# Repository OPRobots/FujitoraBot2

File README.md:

# FujitoraBot2

Versión 2 de FujitoraBot renovando el hardware después de 5 años: un pelín más
rápido, con 24 sensores de línea, giroscopio MPU-6500 y diseño más modular.

## 🏆 Palmarés

| Competición | Resultado | Fecha |
|------------|-----------|-------|
| — | — | — |

## ⚙️ Hardware

| Componente | Detalle |
|-----------|---------|
| **Microcontrolador** | STM32F405RGT6 @ 168 MHz, Cortex-M4F |
| **Sensores** | 24× IR de línea (multiplexados 3×8:1), MPU-6500 (giro ±2000 dps, SPI) |
| **Motores** | 2× DC brushless con ESC BLHeli (OneShot125) |
| **Encoders** | 2× magnéticos en cuadratura (TIM3/TIM4) |
| **Batería** | LiPo 2S/3S, detección automática, divisor ×3.8673 |
| **Ventilador** | Control PWM independiente con rampa de aceleración |
| **Chasis** | PCB propia (KiCad) + impresión 3D |
| **Peso** | — |

## 💻 Software

| Componente | Detalle |
|-----------|---------|
| **Framework** | LibOpenCM3 |
| **Entorno** | PlatformIO |
| **Lenguaje** | C11 |
| **Frecuencia control** | 1000 Hz (TIM5) |
| **Algoritmo** | PID en cascada (velocidad + ángulo + sensores de línea) |
| **Odometría** | Encoders + giroscopio, integración de posición X/Y/θ |
| **Debug** | USART3 @ 115200 + MacroArray (30k registros de telemetría) |

## 📚 Documentación

La documentación técnica completa está en [docs/](docs/):

- [Hardware](docs/01-hardware.md) — MCU, pinout, sensores, actuadores, chasis
- [Arquitectura Software](docs/02-software-architecture.md) — ISRs, DMA, prioridades, flujo
- [Sensores](docs/03-sensors.md) — 24 IR multiplexados, MPU-6500, filtros
- [Movimiento](docs/04-movement.md) — Motores BLHeli, OneShot125, ventilador
- [Control PID](docs/05-control-system.md) — PID cascada, ant-windup, arranque
- [Menú](docs/06-menu-system.md) — Navegación, perfiles, calibración/debug
- [Debug](docs/07-debug-system.md) — USART, macroarray, modos de diagnóstico
- [Calibración](docs/08-calibration.md) — Giroscopio Z, sensores IR, EEPROM
- [EEPROM](docs/09-storage.md) — Flash sector 11, layout de datos
- [Encoders y Giroscopio](docs/10-encoders-gyro.md) — Odometría, MPU-6500, fusión
- [Batería y LEDs](docs/11-battery-leds.md) — Medición, 2S/3S, indicadores
- [Cinemática](docs/12-kinematics.md) — 6 perfiles de velocidad predefinidos
- [Problemas Conocidos](docs/13-known-issues.md) — Issues y bugs documentados

## 🎥 Vídeos

<!-- Enlaces a vídeos del robot en acción -->

## 🔧 Stack Tecnológico

| Herramienta | Tecnología |
|------------|-----------|
| **Microcontrolador** | STM32F405RGT6 |
| **Framework** | LibOpenCM3 |
| **IDE / Build** | PlatformIO |
| **Lenguaje** | C11 |
| **PCB** | KiCad |
| **3D** | SketchUp + STL |

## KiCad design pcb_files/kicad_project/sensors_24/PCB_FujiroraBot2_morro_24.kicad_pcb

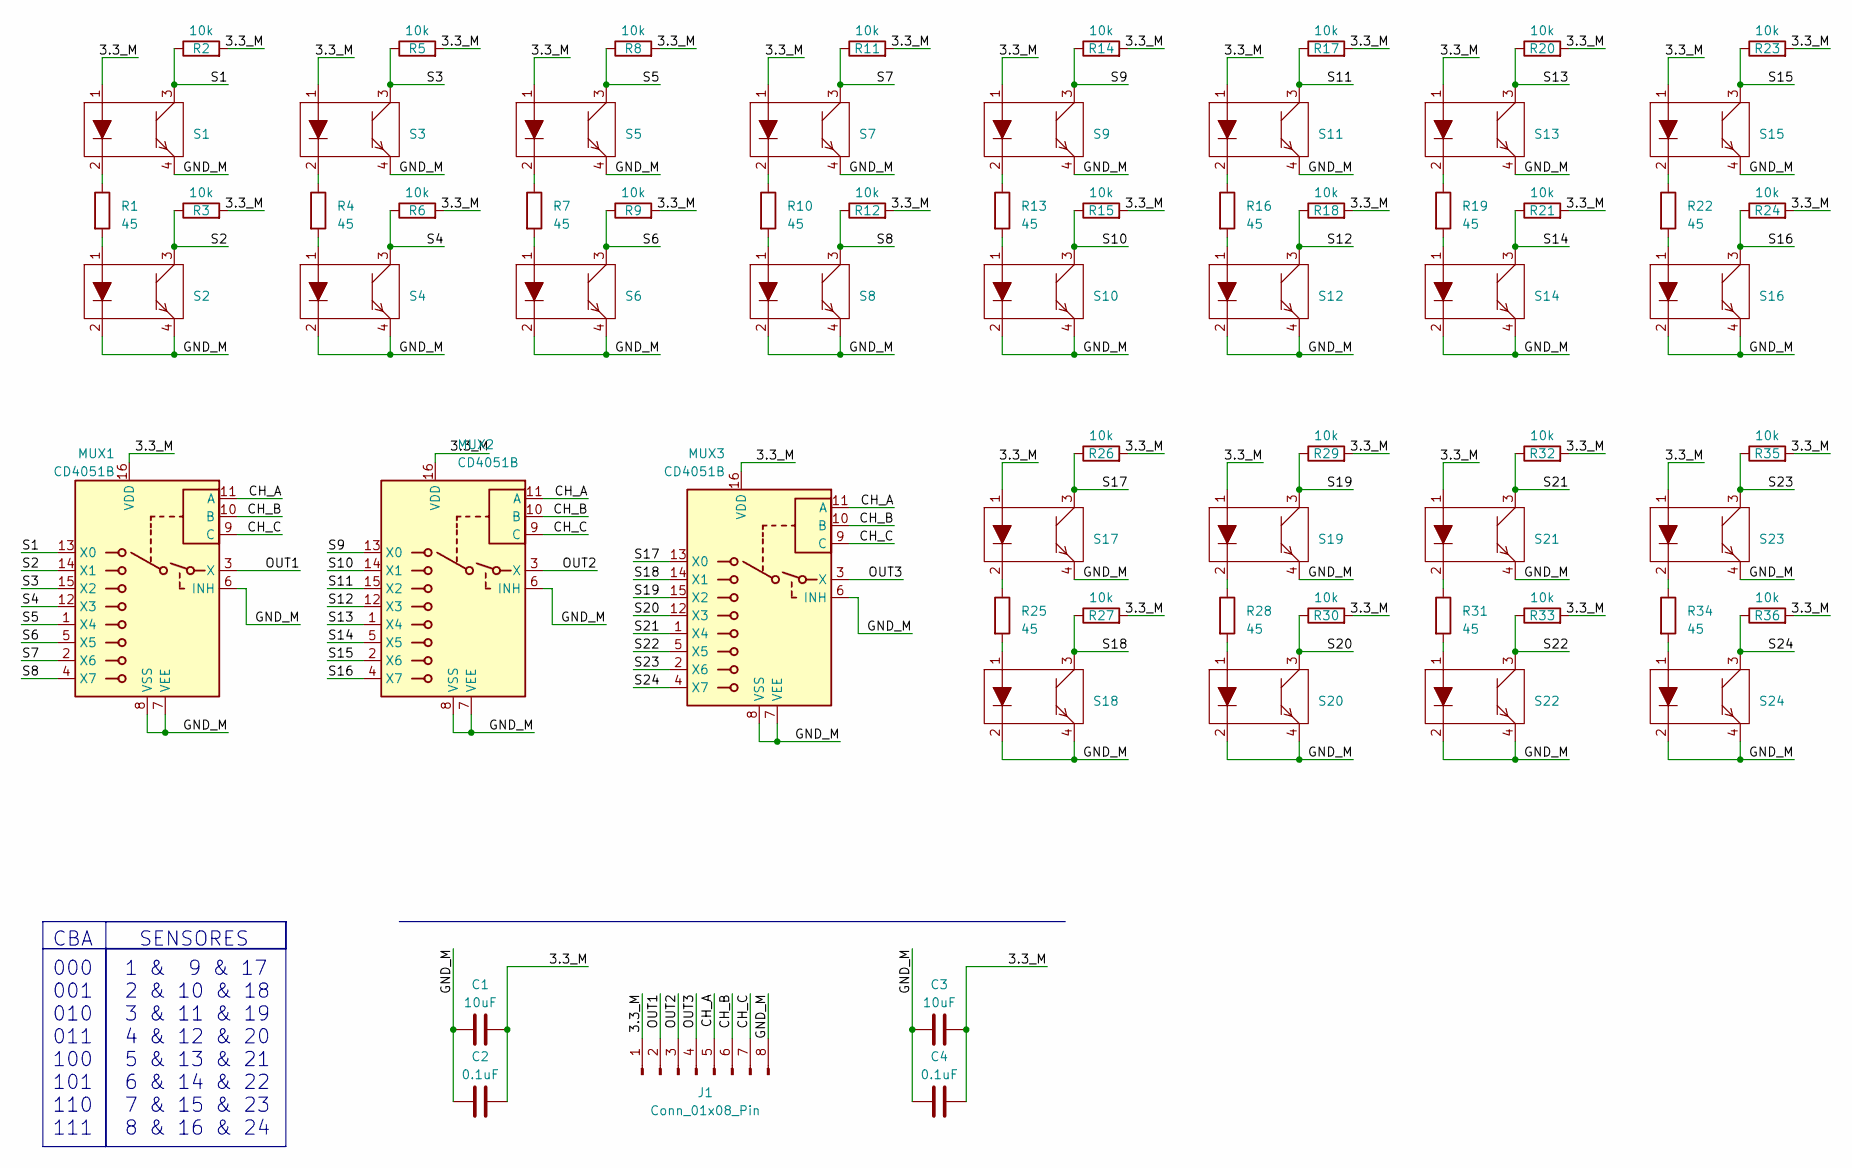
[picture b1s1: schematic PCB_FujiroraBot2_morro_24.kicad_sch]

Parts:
C1, C3: 10uF; C_0805_2012Metric_Pad1.18x1.45mm_HandSolder; LCSC Part # C380331
C2, C4: 0.1uF; C_0805_2012Metric_Pad1.18x1.45mm_HandSolder; LCSC Part # C2847428
J1: Conn_01x08_Pin; Fujitora_pads_morro
MUX1, MUX2, MUX3: CD4051B; MUX_CD4051B; LCSC Part # C3007951
R1, R4, R7, R10, R13, R16, R19, R22, R25, R28, R31, R34: 45; R_0402_1005Metric_Pad0.72x0.64mm_HandSolder; LCSC Part # C3017827
R2, R3, R5, R6, R8, R9, R11, R12, R14, R15, R17, R18, R20, R21, R23, R24, R26, R27, R29, R30, R32, R33, R35, R36: 10k; R_0402_1005Metric_Pad0.72x0.64mm_HandSolder; LCSC Part # C17414
S1, S2, S3, S4, S5, S6, S7, S8, S9, S10, S11, S12, S13, S14, S15, S16, S17, S18, S19, S20, S21, S22, S23, S24: FujitoraBot2_QRE1113; LCSC Part # C81632

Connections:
/3.3_M: C1.1, C2.1, C3.1, C4.1, J1.1, MUX1.16 (VDD), MUX2.16 (VDD), MUX3.16 (VDD), R2.2, R3.2, R5.2, R6.2, R8.2, R9.2, R11.2, R12.2, R14.2, R15.2, R17.2, R18.2, R20.2, R21.2, R23.2, R24.2, R26.2, R27.2, R29.2, R30.2, R32.2, R33.2, R35.2, R36.2, S1.1, S3.1, S5.1, S7.1, S9.1, S11.1, S13.1, S15.1, S17.1, S19.1, S21.1, S23.1
/CH_A: J1.5, MUX1.11 (A), MUX2.11 (A), MUX3.11 (A)
/CH_B: J1.6, MUX1.10 (B), MUX2.10 (B), MUX3.10 (B)
/CH_C: J1.7, MUX1.9 (C), MUX2.9 (C), MUX3.9 (C)
/GND_M: C1.2, C2.2, C3.2, C4.2, J1.8, MUX1.6 (INH), MUX1.7 (VEE), MUX1.8 (VSS), MUX2.6 (INH), MUX2.7 (VEE), MUX2.8 (VSS), MUX3.6 (INH), MUX3.7 (VEE), MUX3.8 (VSS), S1.4, S2.2, S2.4, S3.4, S4.2, S4.4, S5.4, S6.2, S6.4, S7.4, S8.2, S8.4, S9.4, S10.2, S10.4, S11.4, S12.2, S12.4, S13.4, S14.2, S14.4, S15.4, S16.2, S16.4, S17.4, S18.2, S18.4, S19.4, S20.2, S20.4, S21.4, S22.2, S22.4, S23.4, S24.2, S24.4
/OUT1: J1.2, MUX1.3 (X)
/OUT2: J1.3, MUX2.3 (X)
/OUT3: J1.4, MUX3.3 (X)
/S1: MUX1.13 (X0), R2.1, S1.3
/S2: MUX1.14 (X1), R3.1, S2.3
/S3: MUX1.15 (X2), R5.1, S3.3
/S4: MUX1.12 (X3), R6.1, S4.3
/S5: MUX1.1 (X4), R8.1, S5.3
/S6: MUX1.5 (X5), R9.1, S6.3
/S7: MUX1.2 (X6), R11.1, S7.3
/S8: MUX1.4 (X7), R12.1, S8.3
/S9: MUX2.13 (X0), R14.1, S9.3
/S10: MUX2.14 (X1), R15.1, S10.3
/S11: MUX2.15 (X2), R17.1, S11.3
/S12: MUX2.12 (X3), R18.1, S12.3
/S13: MUX2.1 (X4), R20.1, S13.3
/S14: MUX2.5 (X5), R21.1, S14.3
/S15: MUX2.2 (X6), R23.1, S15.3
/S16: MUX2.4 (X7), R24.1, S16.3
/S17: MUX3.13 (X0), R26.1, S17.3
/S18: MUX3.14 (X1), R27.1, S18.3
/S19: MUX3.15 (X2), R29.1, S19.3
/S20: MUX3.12 (X3), R30.1, S20.3
/S21: MUX3.1 (X4), R32.1, S21.3
/S22: MUX3.5 (X5), R33.1, S22.3
/S23: MUX3.2 (X6), R35.1, S23.3
/S24: MUX3.4 (X7), R36.1, S24.3
unnamed: R1.1, S1.2
unnamed: R1.2, S2.1
unnamed: R4.1, S3.2
unnamed: R4.2, S4.1
unnamed: R7.1, S5.2
unnamed: R7.2, S6.1
unnamed: R10.1, S7.2
unnamed: R10.2, S8.1
unnamed: R13.1, S9.2
unnamed: R13.2, S10.1
unnamed: R16.1, S11.2
unnamed: R16.2, S12.1
unnamed: R19.1, S13.2
unnamed: R19.2, S14.1
unnamed: R22.1, S15.2
unnamed: R22.2, S16.1
unnamed: R25.1, S17.2
unnamed: R25.2, S18.1
unnamed: R28.1, S19.2
unnamed: R28.2, S20.1
unnamed: R31.1, S21.2
unnamed: R31.2, S22.1
unnamed: R34.1, S23.2
unnamed: R34.2, S24.1

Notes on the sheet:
SENSORES
000 001 010 011 100 101 110 111
1 & 9 & 17 2 & 10 & 18 3 & 11 & 19 4 & 12 & 20 5 & 13 & 21 6 & 14 & 22 7 & 15 & 23 8 & 16 & 24
CBA

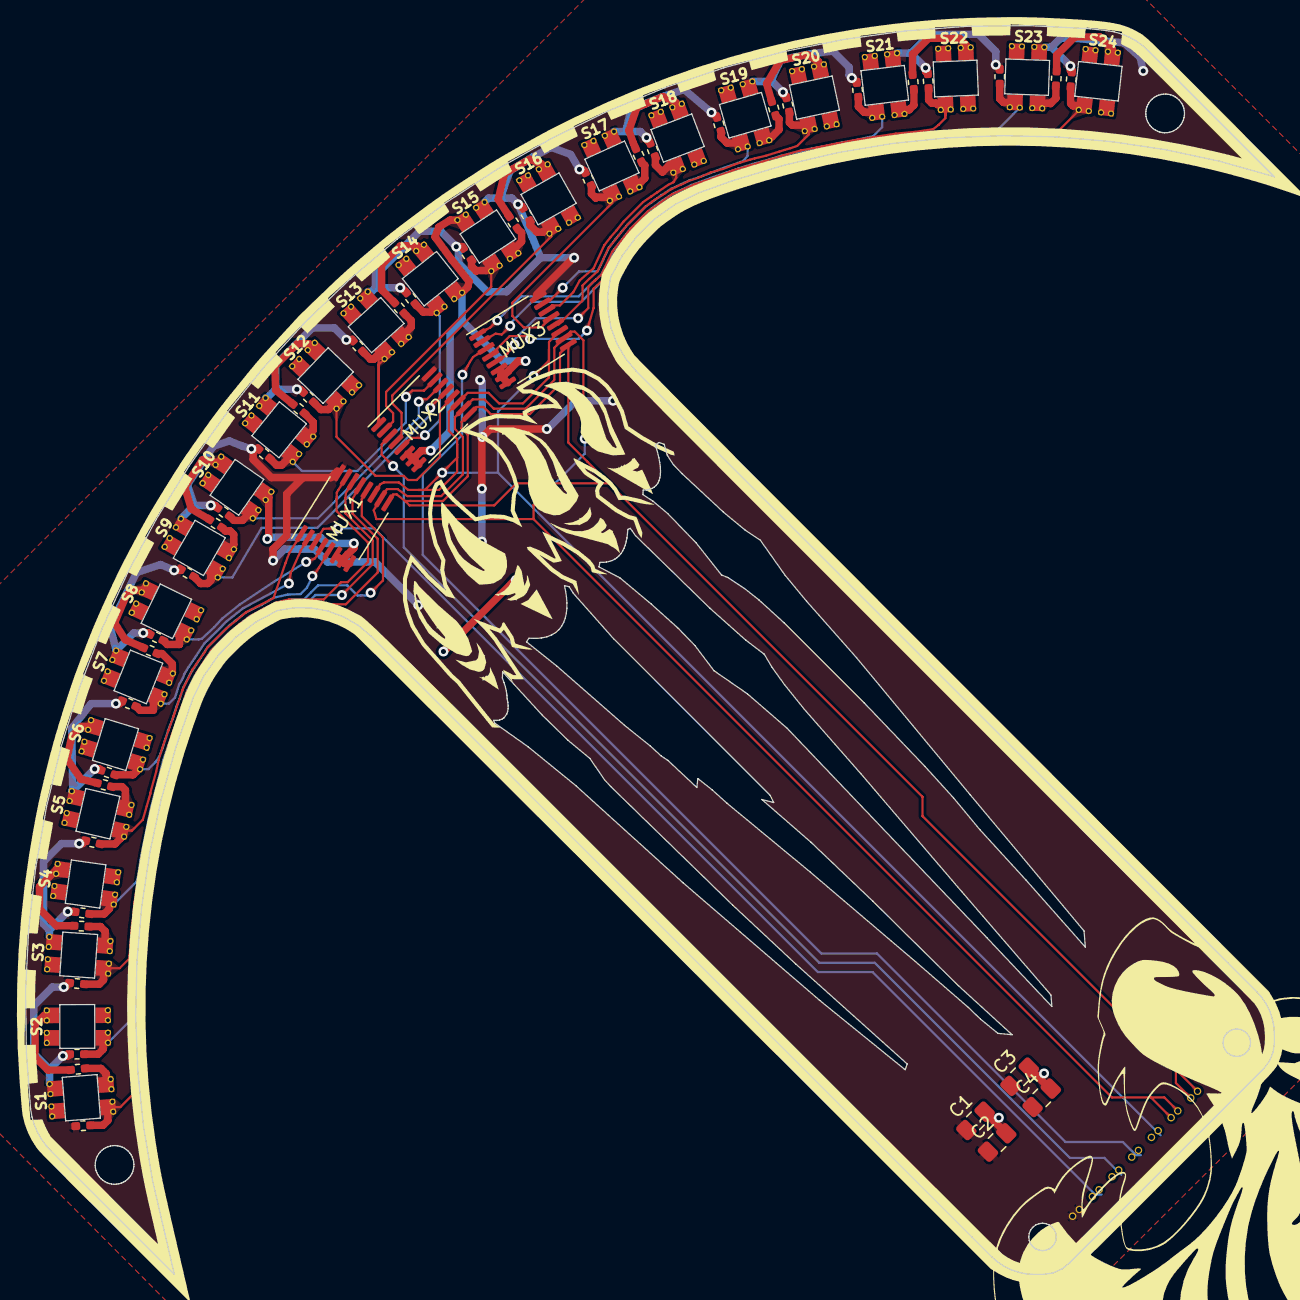
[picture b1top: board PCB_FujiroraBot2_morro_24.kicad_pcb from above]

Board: 2 copper layers, 100.0 x 100.0 mm, 68 parts (1 on the bottom side), 56 nets.

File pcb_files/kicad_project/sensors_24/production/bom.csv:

Designator,Footprint,Quantity,Value,LCSC Part #
"C1, C3",0805,2,10uF,C380331
"C2, C4",0805,2,0.1uF,C2847428
J1,Fujitora_pads_morro,1,Conn_01x08_Pin,
"MUX1, MUX2, MUX3",MUX_CD4051B,3,CD4051B,C3007951
"R1, R10, R13, R16, R19, R22, R25, R28, R31, R34, R4, R7",0402,12,45,C3017827
"R11, R12, R14, R15, R17, R18, R2, R20, R21, R23, R24, R26, R27, R29, R3, R30, R32, R33, R35, R36, R5, R6, R8, R9",0402,24,10k,C17414
"S1, S10, S11, S12, S13, S14, S15, S16, S17, S18, S19, S2, S20, S21, S22, S23, S24, S3, S4, S5, S6, S7, S8, S9",FujitoraBot2_QRE1113,24,~,C81632

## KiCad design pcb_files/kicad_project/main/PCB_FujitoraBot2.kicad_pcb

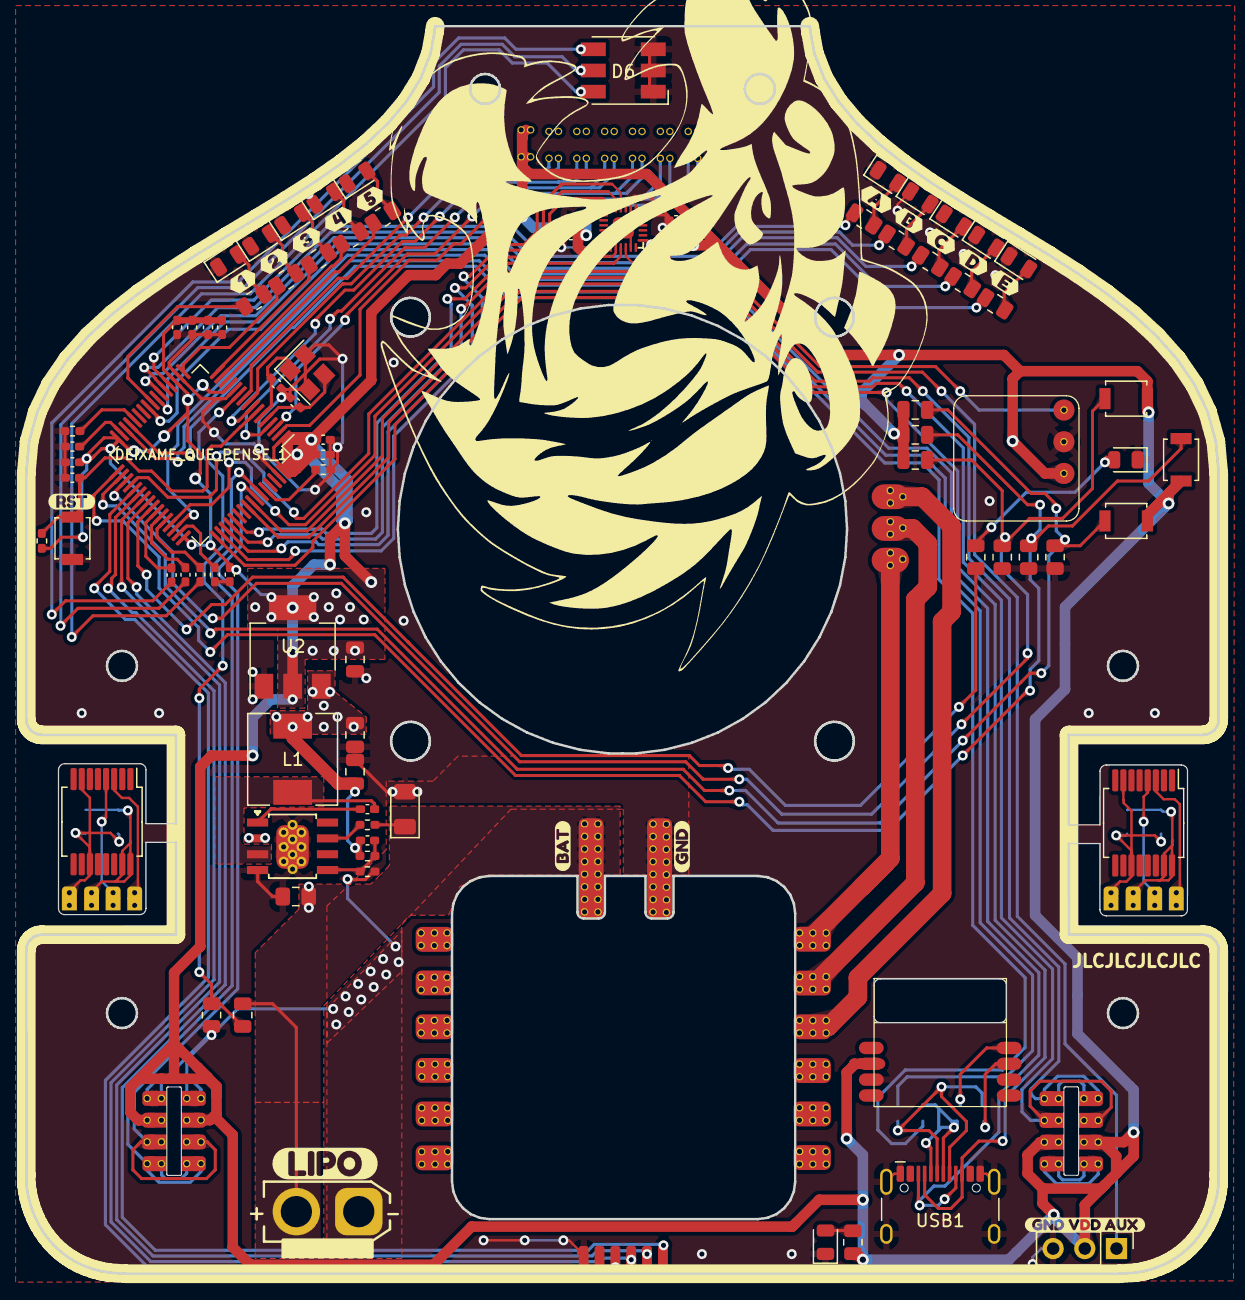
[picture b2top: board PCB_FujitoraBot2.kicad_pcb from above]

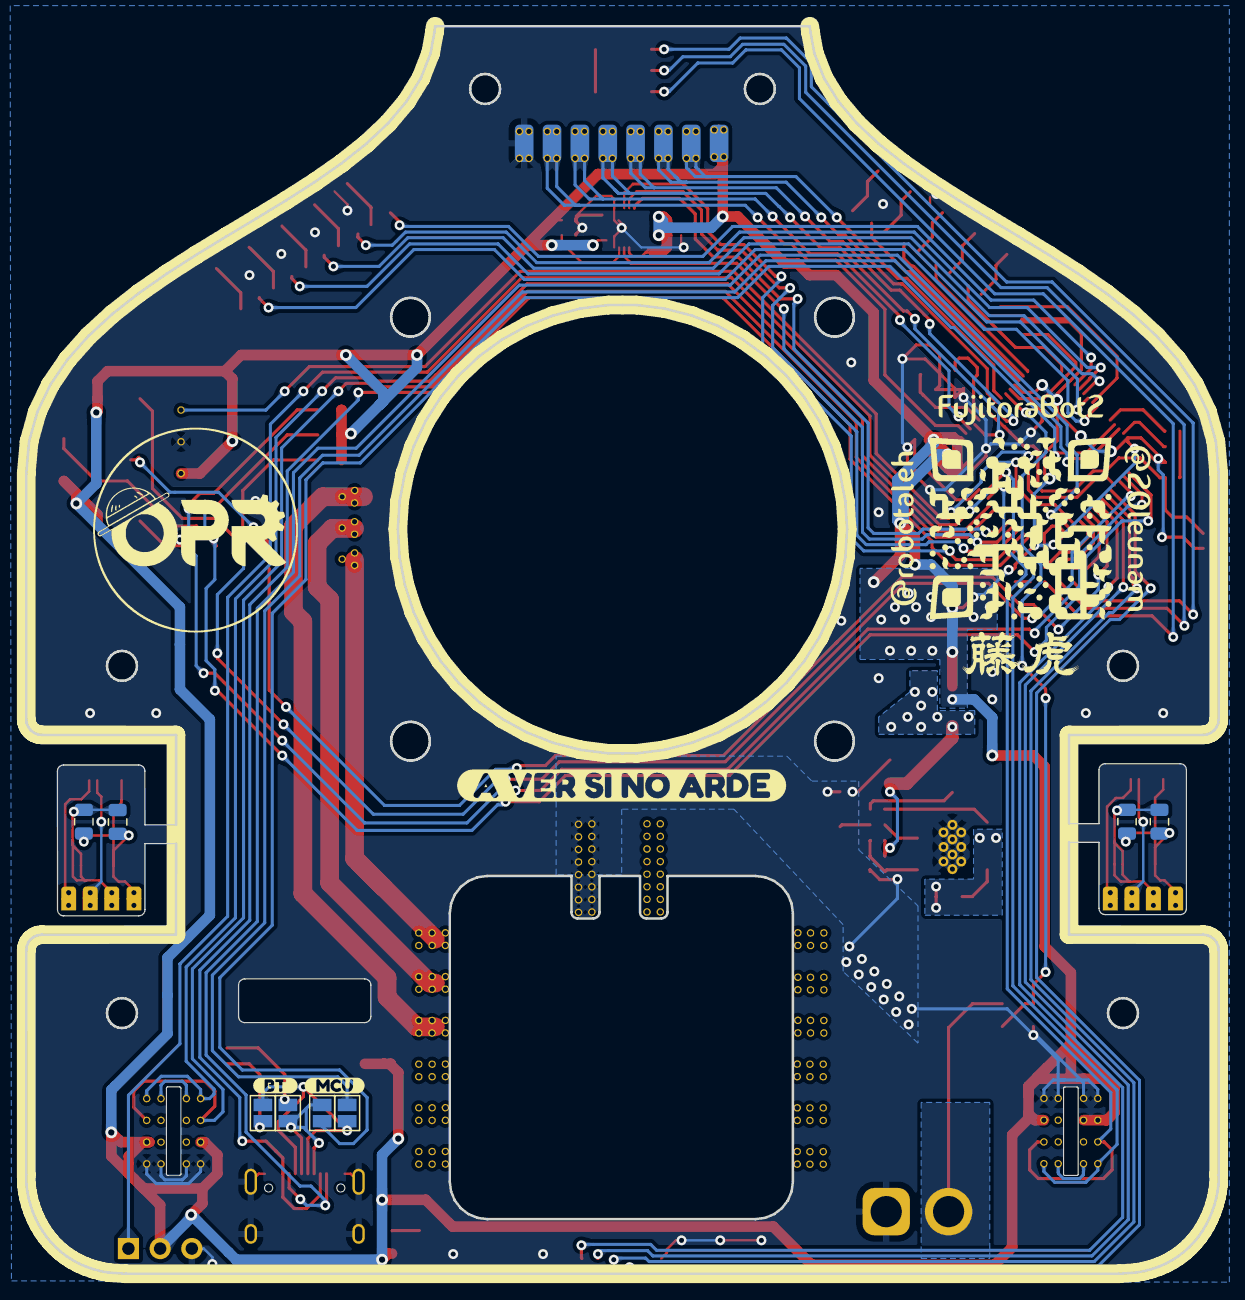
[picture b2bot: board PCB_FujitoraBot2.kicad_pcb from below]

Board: 2 copper layers, 95.6 x 100.0 mm, 117 parts (12 on the bottom side), 88 nets.

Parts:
BATT_1: Conn_01x02_Female; XT30 connector
BT1: Bluetooth_BLE_1x1cm
C1, C20: 4.7uF; C_0402_1005Metric_Pad0.74x0.62mm_HandSolder
C2, C3, C7, C10, C11, C15, C17: 0.1uF; C_0402_1005Metric_Pad0.74x0.62mm_HandSolder
C4, C9: 2.2uF; C_0402_1005Metric_Pad0.74x0.62mm_HandSolder
C5: 20uF; C_0402_1005Metric_Pad0.74x0.62mm_HandSolder
C6: 20pF; C_0402_1005Metric_Pad0.74x0.62mm_HandSolder
C8, C12: 1uF; C_0402_1005Metric_Pad0.74x0.62mm_HandSolder
C13, C18: 1uF; C_0805_2012Metric
C14, C19: 0.1uF; C_0805_2012Metric
C16: 0.01uF; C_0402_1005Metric_Pad0.74x0.62mm_HandSolder
CR1, CR2, CR3, CR7, CR8: 0.1uF; C_0805_2012Metric
CR4, CR5, CR9: 0.1uF; C_0402_1005Metric_Pad0.74x0.62mm_HandSolder
CR6: 0.1uF; C_0805_2012Metric_Pad1.18x1.45mm_HandSolder
CR10: 10uF; C_0805_2012Metric
D1, D2, D3, D4, D5, D7, D8, D9, D10, D11, D12, D13: LED; LED_0805_2012Metric
D6: LED_RGB; LED_RGB_5050-6
D14: D; D_1206_3216Metric
DC-DC1: SOP8_with_gnd_pad
DEIXAME_QUE_PENSE_1: STM32F405RGT6; LQFP-64_10x10mm_P0.5mm
ESC1: ESC_x4_15A; Fujitora_ESC
IC1, IC2: AS5040; SSOP-16_5.3x6.2mm_P0.65mm
J1: MORRO1; Fujitora_pads_morro
JP1, JP2, JP3, JP4: SolderJumper_2_Open; SolderJumper-2_P1.3mm_Open_Pad1.0x1.5mm
J_ENC_1, J_ENC_2: Conn_01x04_Socket; FujitoraBot2_PCBmain_Encoder
J_ENC_1_CONN1, J_ENC_2_CONN1: Conn_01x04_Pin; FujitoraBot2_PCBmodule_encoder
J_ESC1: Conn_01x06_Female; Fujitora_pads_ESC
L1: L; L_Wuerth_HCM-7050
MODULO_START_STOP1: Conn_01x03_Female; IR_Start
MOTOR_1: Conn_01x03_Female; PinHeader_1x03_P2.54mm_Vertical
PIN_AUXILIAR1: Conn_01x03_Female; PinHeader_1x03_P2.54mm_Vertical
R1, R2, R3, R4, R5, R9, R10, R11, R12, R13, R15: 330; R_0805_2012Metric
R6, R7, R8: 330; C_0402_1005Metric_Pad0.74x0.62mm_HandSolder
R14: 47k; R_0402_1005Metric_Pad0.72x0.64mm_HandSolder
R16: 1K; R_0805_2012Metric
R17, R25: 47K; R_0402_1005Metric_Pad0.72x0.64mm_HandSolder
R18, R19, R20, R23, R24: 47K; R_0805_2012Metric
R28: 45K; R_0402_1005Metric_Pad0.72x0.64mm_HandSolder
R29: 100k; R_0402_1005Metric_Pad0.72x0.64mm_HandSolder
R30: 60k; R_0402_1005Metric_Pad0.72x0.64mm_HandSolder
SW1, SW2, SW3: SW_Push; SW_SPST_B3U-1000P
SW4: SW_Reset; SW_SPST_B3U-1000P
U1: MPU-6500; FujitoraBot2_giro_MPU6500
U2: LM1117MP-3.3; SOT-223-3_TabPin2
USB1: HRO-TYPE-C-31-M-12; USB-C ST-Link USART
Y1: Crystal_GND24; Crystal_SMD_TXC_7M-4Pin_3.2x2.5mm
kibuzzard-66B8D5B6: G***; kibuzzard-66B8D5B6
kibuzzard-66B8D6B0: G***; kibuzzard-66B8D6B0
kibuzzard-66B8D59D: G***; kibuzzard-66B8D59D
kibuzzard-66B8D625: G***; kibuzzard-66B8D625
kibuzzard-66B8D672: G***; kibuzzard-66B8D672
kibuzzard-66B8D700: G***; kibuzzard-66B8D700
kibuzzard-66B8DA7F: G***; kibuzzard-66B8DA7F
kibuzzard-66B8DA98: G***; kibuzzard-66B8DA98
kibuzzard-66B8DBE7: G***; kibuzzard-66B8DBE7
kibuzzard-66B8DBFF: G***; kibuzzard-66B8DBFF
kibuzzard-66B8DC0B: G***; kibuzzard-66B8DC0B
kibuzzard-66B8DC05: G***; kibuzzard-66B8DC05
kibuzzard-66B8DC13: G***; kibuzzard-66B8DC13
kibuzzard-66B8DD07: G***; kibuzzard-66B8DD07
kibuzzard-66B8DD11: G***; kibuzzard-66B8DD11
kibuzzard-66B8DD29: G***; kibuzzard-66B8DD29
kibuzzard-66B8DD65: G***; kibuzzard-66B8DD65
kibuzzard-66B8DD76: G***; kibuzzard-66B8DD76

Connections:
+3V3: BT1.2 (VCC), C1.2, C2.2, C3.2, C7.2, C8.2, C10.2, C11.2, C12.2, C15.2, C16.2, C20.2, CR1.1, CR2.1, CR3.1, CR10.1, DEIXAME_QUE_PENSE_1.1 (VBAT), DEIXAME_QUE_PENSE_1.13 (VDDA), DEIXAME_QUE_PENSE_1.19 (VDD), DEIXAME_QUE_PENSE_1.32 (VDD), DEIXAME_QUE_PENSE_1.48 (VDD), DEIXAME_QUE_PENSE_1.64 (VDD), J1.8, J_ENC_1.2, J_ENC_2.2, MODULO_START_STOP1.1, PIN_AUXILIAR1.2, R14.2, R16.1, SW1.2, SW2.2, SW3.2, U1.8 (VDDIO), U1.13 (VDD), U2.2 (VO)
+5V: CR7.2, CR8.1, CR9.1, L1.2, R30.1, U2.3 (VI)
/ANLG_BAT: DEIXAME_QUE_PENSE_1.11 (PC3), R23.2, R24.1
/AUX: DEIXAME_QUE_PENSE_1.45 (PA12), PIN_AUXILIAR1.1
/BATT: BATT_1.2, CR6.2, D14.1 (K), DC-DC1.2 (VIN), ESC1.20 (VCC), R23.1, R29.2
/BOOT: DEIXAME_QUE_PENSE_1.60 (BOOT0), R17.1
/ENC_1_3.3: C13.1, C14.1, IC1.15 (VDD3V3), IC1.16 (VDD5V), J_ENC_1_CONN1.2
/ENC_1_A: DEIXAME_QUE_PENSE_1.59 (PB7), J_ENC_1.4
/ENC_1_A_CONN: IC1.3 (A_LSB_U), J_ENC_1_CONN1.4
/ENC_1_B: DEIXAME_QUE_PENSE_1.58 (PB6), J_ENC_1.3
/ENC_1_B_CONN: IC1.4 (B_DIR_V), J_ENC_1_CONN1.3
/ENC_1_GND: C13.2, C14.2, IC1.7 (VSS), IC1.11 (CSN), J_ENC_1_CONN1.1
/ENC_2_3.3: C18.1, C19.1, IC2.15 (VDD3V3), IC2.16 (VDD5V), J_ENC_2_CONN1.2
/ENC_2_A: DEIXAME_QUE_PENSE_1.57 (PB5), J_ENC_2.4
/ENC_2_A_CONN: IC2.3 (A_LSB_U), J_ENC_2_CONN1.4
/ENC_2_B: DEIXAME_QUE_PENSE_1.56 (PB4), J_ENC_2.3
/ENC_2_B_CONN: IC2.4 (B_DIR_V), J_ENC_2_CONN1.3
/ENC_2_GND: C18.2, C19.2, IC2.7 (VSS), IC2.11 (CSN), J_ENC_2_CONN1.1
/ESC_M1_R: ESC1.7 (M3_R), MOTOR_1.3
/ESC_M1_S: ESC1.8 (M3_S), MOTOR_1.2
/ESC_M1_T: ESC1.9 (M3_T), MOTOR_1.1
/LED_1: DEIXAME_QUE_PENSE_1.14 (PA0), R1.1
/LED_2: DEIXAME_QUE_PENSE_1.15 (PA1), R2.1
/LED_3: DEIXAME_QUE_PENSE_1.16 (PA2), R3.1
/LED_4: DEIXAME_QUE_PENSE_1.17 (PA3), R4.1
/LED_5: DEIXAME_QUE_PENSE_1.20 (PA4), R9.1
/LED_6: DEIXAME_QUE_PENSE_1.21 (PA5), R10.1
/LED_7: DEIXAME_QUE_PENSE_1.22 (PA6), R11.1
/LED_8: DEIXAME_QUE_PENSE_1.23 (PA7), R12.1
/LED_9: DEIXAME_QUE_PENSE_1.24 (PC4), R5.1
/LED_10: DEIXAME_QUE_PENSE_1.25 (PC5), R13.1
/LED_AUX: DEIXAME_QUE_PENSE_1.41 (PA8), R15.1
/MENU_ABAJO: CR2.2, DEIXAME_QUE_PENSE_1.34 (PB13), R19.1, SW2.1
/MENU_ARRIBA: CR1.2, DEIXAME_QUE_PENSE_1.35 (PB14), R18.1, SW1.1
/MENU_ENTER: CR3.2, DEIXAME_QUE_PENSE_1.33 (PB12), R20.1, SW3.1
/MUX_A: DEIXAME_QUE_PENSE_1.2 (PC13), J1.2
/MUX_B: DEIXAME_QUE_PENSE_1.3 (PC14), J1.3
/MUX_C: DEIXAME_QUE_PENSE_1.4 (PC15), J1.4
/MotorD: DEIXAME_QUE_PENSE_1.37 (PC6), J_ESC1.3
/MotorI: DEIXAME_QUE_PENSE_1.38 (PC7), J_ESC1.4
/MotorS1: DEIXAME_QUE_PENSE_1.39 (PC8), J_ESC1.5
/MotorS2: DEIXAME_QUE_PENSE_1.40 (PC9), J_ESC1.6
/RGB_B: DEIXAME_QUE_PENSE_1.44 (PA11), R6.1
/RGB_G: DEIXAME_QUE_PENSE_1.43 (PA10), R7.1
/RGB_R: DEIXAME_QUE_PENSE_1.42 (PA9), R8.1
/RST: CR4.1, DEIXAME_QUE_PENSE_1.7 (NRST), R14.1, SW4.1
/RX: JP2.2 (B), JP4.2 (B), USB1.6 (DP1), USB1.8 (DP2)
/SPI_MISO: DEIXAME_QUE_PENSE_1.52 (PC11), U1.9 (AD0/SDO)
/SPI_MOSI: DEIXAME_QUE_PENSE_1.53 (PC12), U1.24 (SDA/SDI)
/SPI_NSS: DEIXAME_QUE_PENSE_1.50 (PA15), U1.22 (nCS)
/SPI_SCK: DEIXAME_QUE_PENSE_1.51 (PC10), U1.23 (SCL/SCLK)
/START_STOP: DEIXAME_QUE_PENSE_1.36 (PB15), MODULO_START_STOP1.3
/SWCLK: DEIXAME_QUE_PENSE_1.49 (PA14), USB1.4 (CC1), USB1.10 (CC2)
/SWDIO: DEIXAME_QUE_PENSE_1.46 (PA13), USB1.3 (SBU2), USB1.9 (SBU1)
/S_DE_X8: DEIXAME_QUE_PENSE_1.10 (PC2), J1.7
/S_FR_X8: DEIXAME_QUE_PENSE_1.9 (PC1), J1.6
/S_IZ_X8: DEIXAME_QUE_PENSE_1.8 (PC0), J1.5
/TX: JP1.2 (B), JP3.1 (A), USB1.5 (DN2), USB1.7 (DN1)
GND: BATT_1.1, BT1.3 (GND), C1.1, C2.1, C3.1, C4.1, C5.1, C6.1, C7.1, C8.1, C9.1, C10.1, C11.1, C12.1, C15.1, C16.1, C17.1, C20.1, CR4.2, CR6.1, CR7.1, CR8.2, CR10.2, D1.1 (K), D2.1 (K), D3.1 (K), D4.1 (K), D5.1 (K), D6.1 (RK), D6.2 (GK), D6.3 (BK), D7.1 (K), D8.1 (K), D9.1 (K), D10.1 (K), D11.1 (K), D12.1 (K), D13.1 (K), D14.2 (A), DC-DC1.4 (GND), DC-DC1.9 (EPAD), DEIXAME_QUE_PENSE_1.12 (VSSA), DEIXAME_QUE_PENSE_1.18 (VSS), DEIXAME_QUE_PENSE_1.63 (VSS), ESC1.19 (GND), J1.1, J_ENC_1.1, J_ENC_2.1, J_ESC1.1, MODULO_START_STOP1.2, PIN_AUXILIAR1.3, R17.2, R18.2, R19.2, R20.2, R24.2, R25.2, R28.1, SW4.2, U1.11 (FSYNC), U1.18 (GND), U1.20 (RESV), U2.1 (GND), USB1.1 (GND), USB1.12 (GND), USB1.13 (SHIELD), Y1.2, Y1.4
unnamed: BT1.8 (RX), JP3.2 (B)
unnamed: BT1.7 (TX), JP4.1 (A)
unnamed: D1.2 (A), R1.2
unnamed: D2.2 (A), R2.2
unnamed: D3.2 (A), R3.2
unnamed: D4.2 (A), R4.2
unnamed: D5.2 (A), R5.2
unnamed: D6.4 (BA), R8.2
unnamed: D6.5 (GA), R7.2
unnamed: D6.6 (RA), R6.2
unnamed: D7.2 (A), R9.2
unnamed: D8.2 (A), R10.2
unnamed: D9.2 (A), R11.2
unnamed: D10.2 (A), R12.2
unnamed: D11.2 (A), R13.2
unnamed: D12.2 (A), R15.2
unnamed: D13.2 (A), R16.2
unnamed: CR5.2, DC-DC1.1 (BST)
unnamed: DC-DC1.7 (EN), R29.1
unnamed: CR9.2, DC-DC1.5 (FB), R28.2, R30.2
unnamed: CR5.1, DC-DC1.3 (SW), L1.1
unnamed: DEIXAME_QUE_PENSE_1.28 (PB2/BOOT1), R25.1
unnamed: DEIXAME_QUE_PENSE_1.29 (PB10), JP1.1 (A)
unnamed: DEIXAME_QUE_PENSE_1.30 (PB11), JP2.1 (A)
unnamed: C5.2, DEIXAME_QUE_PENSE_1.5 (PH0/OSC_IN), Y1.3
unnamed: C6.2, DEIXAME_QUE_PENSE_1.6 (PH1/OSC_OUT), Y1.1
unnamed: C9.2, DEIXAME_QUE_PENSE_1.31 (VCAP_1)
unnamed: C4.2, DEIXAME_QUE_PENSE_1.47 (VCAP_2)
unnamed: C17.2, U1.10 (REGOUT)

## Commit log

2024-09-05 Añade estructura de carpetas inicial
2024-09-05 Añade proyectos de kicad y gerbers
2024-09-05 Añade custom_libraries a los proyectos de kicad
2024-09-06 Añade código estable de FujitoraBot (1)
2024-09-06 Añade adaptación inicial para la v2
2024-09-11 Continua la puesta en marcha de Fujitora comprobando que todo funcione individualmente
2024-09-14 Actualiza los MICROMETERS_PER_TICK de los encoders
2024-09-14 Actualiza iniciación de ESC y gestión de motores
2024-09-14 Corrige función de mostrado de batería
2024-09-14 Ajusta lado y dirección de los encoders
2024-09-14 Aumenta el delay entre asignaciones de sensores
2024-09-14 Mejora gestión de botones, calibración de sensores y añade detección de tipo de LiPo
2024-09-15 Realiza adaptación general de código para primera ejecucuión correcta mediante %PWM
2024-09-18 Elimina control de intersecciones de robotracer
2024-09-18 Actualiza gestión de encoders para usar milímetros
2024-09-18 Mejora arranque y parada de ventilador de succión
2024-09-18 Actualiza, una vez más (!), el orden de los mux
2024-09-20 Mejora el control general del robot y corrige bugs para permitir reinicio de carrera sin apagar el robot
2024-09-21 Añade cálculo de posición cartesiana a los encoders
2024-09-21 Actualiza el menú de velocidades añadiendo una extra
2024-09-21 Vuelve a actualizar el orden de los sensores (wtff?)
2024-09-21 Corrige el cálculo de la posición cartesiana del robot
2024-09-21 Añade comprobación y aviso de linea centrada al iniciar
2024-09-25 Ajusta Ks PID linea y mejora gestión de macroarrays y reseteo de angulo de encoders en control
2024-09-28 Ajusta PID de sensores de línea
2024-09-28 Añade control para aplicar corrección angular solo cuando se mueva
2024-09-28 Ajusta el porcentaje de función de las kinematics
2024-09-30 Corrige orden de los macroarrays
2024-10-04 Aplica la calibración de los nuevos encoders
2024-10-04 Elimina filtro de velocidad obtenida por los encoders
2024-10-04 Elimina la parada de seguridad por tiempo (ahora se para por Mando IR)
2024-10-04 Actualiza las kinematics del modo PWM
2024-10-04 Añade log de voltage linear y angular
2024-10-04 Añade imagenes de FujitoraBot2
2024-10-07 Ajusta la velocidad de succión en modo HAKI
2024-11-20 Reduce el PWM mínimo de los motores
2024-11-20 Activa el debug por gráfica y añade batería al log
2025-02-12 Añade selección de uso de sensores en analógico o digital mediante menú
2025-02-27 Activa modo carrera (5s) y corrige fallos menores
2025-09-04 Realiza cambios para la primera prueba de FujiFast
2025-09-05 Ajusta el timer de control principal para 2kHz
2025-09-05 Añade labels a los macroarrays
2025-09-05 Amplía el rango de validación de sensores
2025-09-30 Actualiza velocidades
2025-10-03 Ajusta velocidades y PID para la OSHWDem25
2025-10-29 Modifica PIDs succion en velocidad 5 y quita el bigger filtro
2025-10-30 Añade control de BiggerFilter a lectura de sensores
2025-10-30 Ajusta valores de ventilador
2026-06-25 Añade documentación general y análisis de potenciales problemas
2026-06-25 Actualiza imagen a ruta relativa
2026-06-25 Añade las imágenes perdidas a docs
